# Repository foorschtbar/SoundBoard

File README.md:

# SoundBoard

A simple PCB with two audio drivers, a SD card reader and a ESP32 microcontroller to play sounds via MQTT.

## Features
- On factory settings or no known WiFi SSID is found, device starts in AP mode
  - To stay in AP mode, leave the SSID and password empty
- The LED show the status of the device
  - `Orange`: Booting
  - `Blue`: Connecting to WiFi
  - `Green`: Connected to existing WiFi
  - `Violet`: Started WiFi AP
  - `Red`: No connection to WiFi
  - `White`: Web or MQTT activity
- The device can be controlled via MQTT:
  - Subscripte to `<prefix>/status` to get the status of the device
  - Publish to `<prefix>/cmd` to play a sound
    - `{"play": "filename.mp3", "volume": 50, "balance": 0}` (volume and balance are optional)
    - `{"tts": "Hello World", "lang": "de"}`

## Getting Started

- Default WiFi SSID: `SoundBoard`
- Default WiFi Password: `12345678x!`
  
## Hardware

### Case

- The case could be found on [Printables](https://www.printables.com/model/1072334-soundboard).

### PCB

- The PCB was designed with KiCad and could be found in the `pcb` directory.

## Development
### Frontend development

- Start the frontend development server with `python .\webserver.py` in the `html` directory.
- Open the browser at `http://localhost:8000/` to see the frontend.
- Set manual a cookie with `overwrite-host` to the hostname or ip of the device and reload the page.

### ToDos/Improvement Ideas

- [ ] Add a priority flag to the MQTT messages. Stop the current playback only if the priority is higher than the current one.
- [ ] Sync volume and balance fader across all clients
- [ ] Enable/Disable Playback/Stop buttons based on the current state
- [ ] Add addidtional MQTT topics with hostname for status und command
- [ ] Refactor Code in more separat files
- [ ] Maybe: Option to queue playbacks
- [x] Send file list in multiple messages
- [x] If we had valid settings, but in fallback AP mode, try to connect to the last known wifi periodically
- [x] Download audiofiles from the webinterface
- [x] Replace play/delete/download with icons?
- [x] Add tailing slash to the topic prefix
- [x] Save authentication in cookie/webstore
- [x] Add credentials to post requests
- [x] Improve MQTT reconnection and resubscription
- [x] Improve MQTT reconnection after boot when no connection is available
- [x] Make MQTT status topic more "chatty"

## Links
- [ESP32 Based Internet Radio using MAX98357A I2S Amplifier Board](https://circuitdigest.com/microcontroller-projects/esp32-based-internet-radio-using-max98357a-i2s-amplifier-board)
- [I2S Sound Tutorial for ESP32 - DIYI0T](https://diyi0t.com/i2s-sound-tutorial-for-esp32/)
- [schreibfaul1/ESP32-audioI2S: Play mp3 files from SD via I2S](https://github.com/schreibfaul1/ESP32-audioI2S)
- [ESP32 Pinout Reference: Which GPIO pins should you use? | Random Nerd Tutorials](https://randomnerdtutorials.com/esp32-pinout-reference-gpios/)
- [ESP32 partition calculator: Easily Calculate ESP32 Memory and Partition Sizes](https://esp32.jgarrettcorbin.com/)

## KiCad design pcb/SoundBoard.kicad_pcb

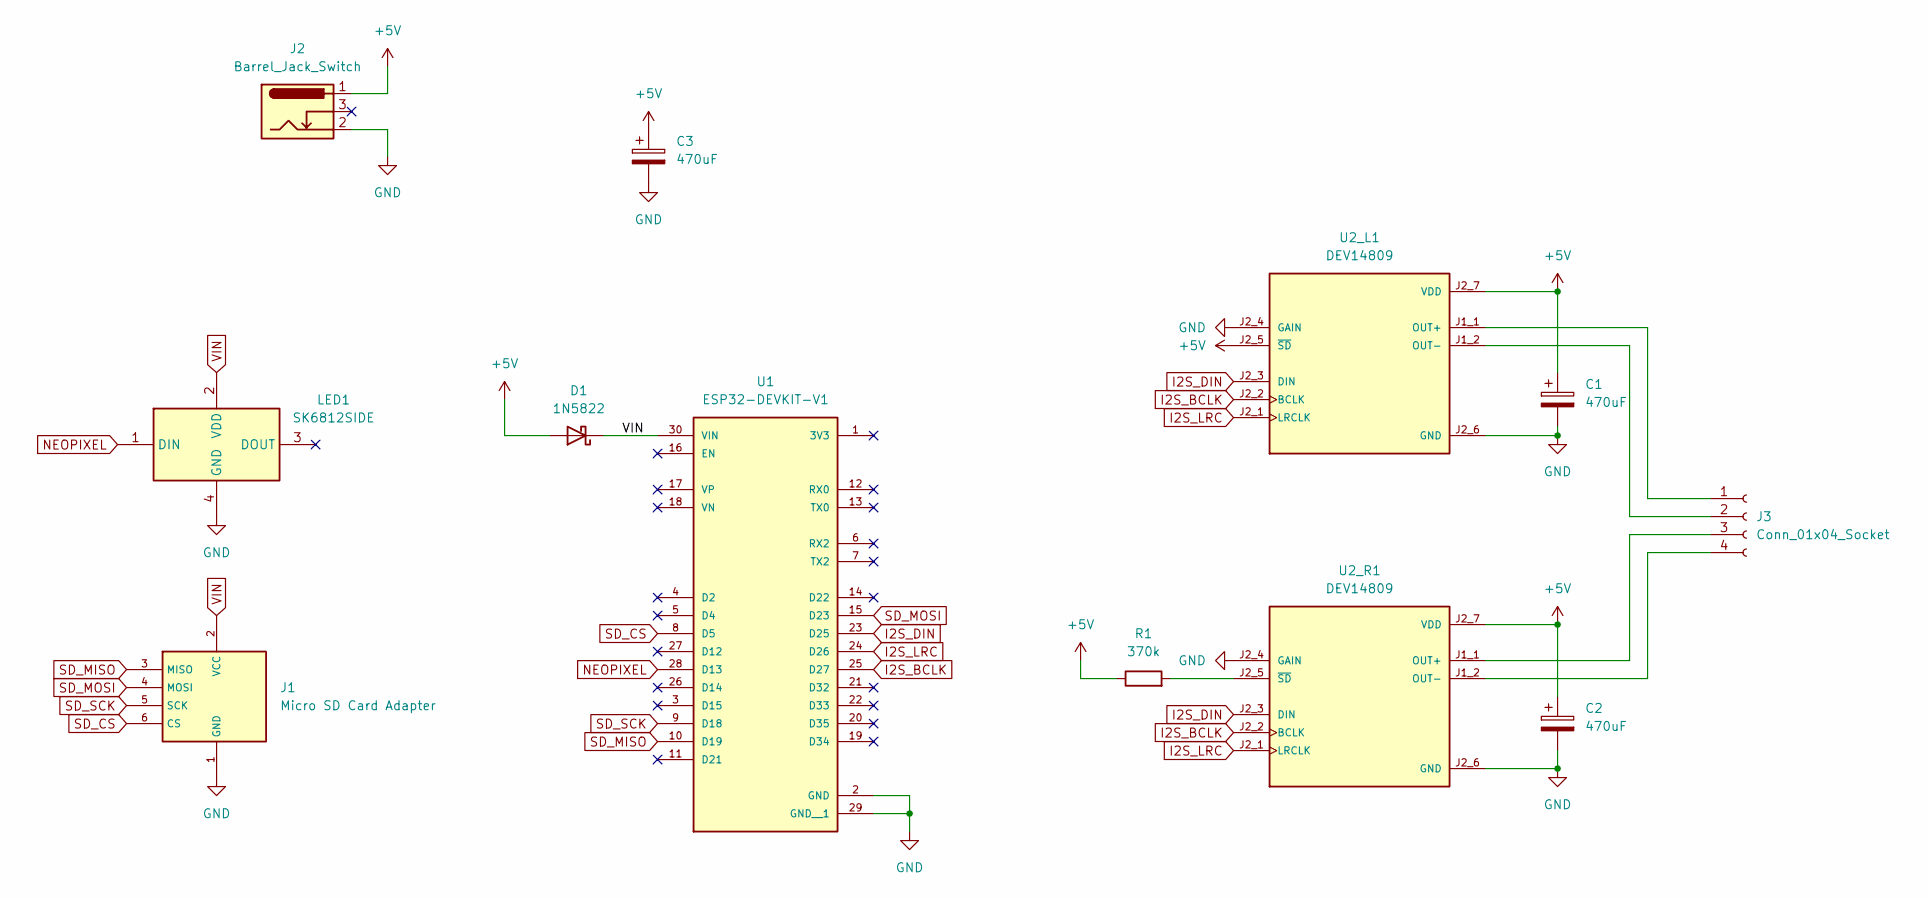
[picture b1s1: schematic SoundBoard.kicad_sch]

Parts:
C1, C2, C3: 470uF; C_Elec_6.3x7.7
D1: 1N5822; D_SMA_Handsoldering
J1: Micro SD Card Adapter; SDCardAdapter
J2: Barrel_Jack_Switch; BarrelJack_Horizontal
J3: Conn_01x04_Socket; TerminalBlock_Phoenix_MKDS-1,5-4-5.08_1x04_P5.08mm_Horizont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
LED1: SK6812SIDE; Manufacturer_Part_Number SK6812SIDE
R1: 370k; R_0805_2012Metric_Pad1.20x1.40mm_HandSolder
U1: ESP32-DEVKIT-V1; ESP32_DEVKIT_V1; PARTREV N/A
U2_L1, U2_R1: DEV14809; MAX98357A; PARTREV 1.2

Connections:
+5V: C1.1, C2.1, C3.1, D1.2 (A), J2.1, R1.1, U2_L1.J2_5 (~SD), U2_L1.J2_7 (VDD), U2_R1.J2_7 (VDD)
GND: C1.2, C2.2, C3.2, J1.1 (GND), J2.2, LED1.4 (GND), U1.2 (GND), U1.29 (GND__1), U2_L1.J2_4 (GAIN), U2_L1.J2_6 (GND), U2_R1.J2_4 (GAIN), U2_R1.J2_6 (GND)
I2S_BCLK: U1.25 (D27), U2_L1.J2_2 (BCLK), U2_R1.J2_2 (BCLK)
I2S_DIN: U1.23 (D25), U2_L1.J2_3 (DIN), U2_R1.J2_3 (DIN)
I2S_LRC: U1.24 (D26), U2_L1.J2_1 (LRCLK), U2_R1.J2_1 (LRCLK)
NEOPIXEL: LED1.1 (DIN), U1.28 (D13)
unnamed: J3.1, U2_L1.J1_1 (OUT+)
unnamed: J3.2, U2_L1.J1_2 (OUT-)
unnamed: J3.3, U2_R1.J1_1 (OUT+)
unnamed: J3.4, U2_R1.J1_2 (OUT-)
unnamed: R1.2, U2_R1.J2_5 (~SD)
SD_CS: J1.6 (CS), U1.8 (D5)
SD_MISO: J1.3 (MISO), U1.10 (D19)
SD_MOSI: J1.4 (MOSI), U1.15 (D23)
SD_SCK: J1.5 (SCK), U1.9 (D18)
VIN: D1.1 (K), J1.2 (VCC), LED1.2 (VDD), U1.30 (VIN)

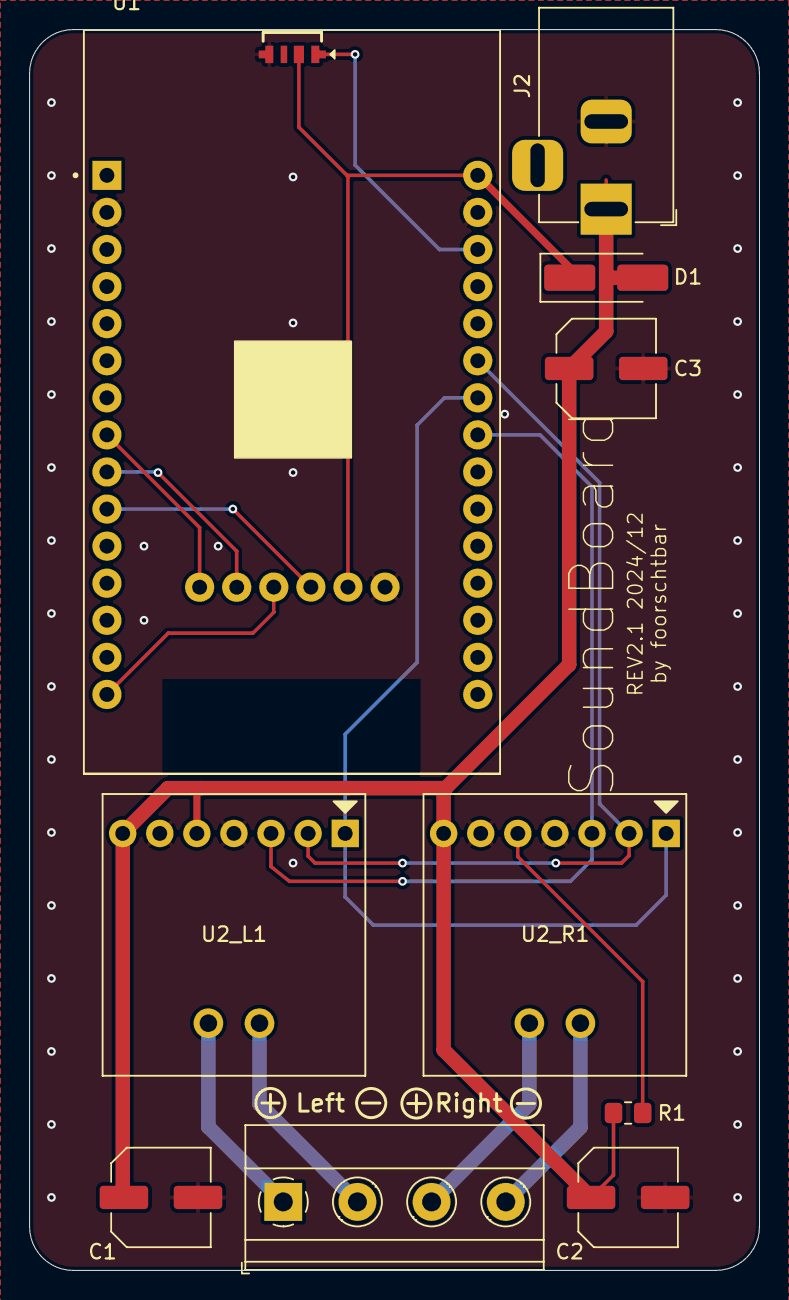
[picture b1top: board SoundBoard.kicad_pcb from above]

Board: 2 copper layers, 50.0 x 85.0 mm, 12 parts (1 on the bottom side), 16 nets.

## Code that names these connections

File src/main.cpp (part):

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
// I2S Pins
#define I2S_DOUT 25
#define I2S_LRC 26
#define I2S_BCLK 27
// SD Card Pins
#define SD_CS 5
#define SPI_SCK 18
#define SPI_MISO 19
#define SPI_MOSI 23
// Other Pins
#define LED 2 // Blue onboard LED
#define NEOPIXEL 13

// Defaul values
#define BRIGHTNESS_DEFAULT 50
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  readSettings();

  // SD Card
  pinMode(SD_CS, OUTPUT);
  digitalWrite(SD_CS, HIGH);
  SPI.begin(SPI_SCK, SPI_MISO, SPI_MOSI);
  SD.begin(SD_CS);
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  logln(F("WebSocket server started"));

  // Audio init
  audio.setPinout(I2S_BCLK, I2S_LRC, I2S_DOUT);
  audio.setVolume(settings_volume);
  audio.setBalance(settings_balance * -1);

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
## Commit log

2024-10-11 Inital commit
2024-10-11 Finished WebUI
2024-10-11 Fixed left channel
2024-10-13 Moved html to separate file
2024-10-13 Fixed WDT Reset problem with SingleLED lib (ocurs on notFound request O.o)
2024-10-14 Moved SingleLED lib
2024-10-14 Fixed fwupdate response
2024-10-14 Improved WebUI
2024-10-14 Added MQTT settings
2024-10-14 Improved SingeLED lib
2024-10-14 Added MQTT implemention
2024-10-15 Added reconnection and resubscription for MQTT
2024-10-16 Small WebUI changes
2024-10-16 MQTT improvments
    - Added LWT
    - Added RSSI2Quality
    - Send statusupdates every 30s
    - Bugfixes
2024-10-17 Improved status messages
2024-10-17 Added TTS
2024-10-20 Finished PCB Layout
2024-10-26 Fixed problem with heap by moving html content to gziped binary flash content
2024-10-28 Fixed a problem where the LED was getting darker and darker
2024-10-28 Added auth to file/fw uploads, improved css and popup
2024-10-28 Small improvments...
2024-11-02 Improved PCBs (REV2.0)
2024-11-02 Fixed MQTT crash in AP mode
2024-11-02 Updated ESP32-AudioI2S lib
2024-11-02 Added blink with temporary color
2024-11-02 Added reboot after timeout in AP mode when SSID is configured
2024-11-13 Added download, icons and tailing slash to the topic prefix
2024-12-03 PCB Rev 2.1
2024-12-03 Improved FS mounting
2024-12-04 Added playback stop button to WebUI
2024-12-04 Update README with default WiFi credentials and new ToDos
2024-12-10 Fixed settings saving
2024-12-11 Improved file list rendering
2024-12-15 Update PCB
2024-12-15 Add TTS example to README
